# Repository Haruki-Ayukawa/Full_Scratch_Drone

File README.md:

# Full_Scratch_Drone
## 概要
キットを購入するのではなく<br>
- KiCADで設計し表面実装したESP32搭載制御基板
- 3DCADで設計し3Dプリンタで造形したフレーム
- AmazonやRCヘリドローン専門ショップで購入したモータ・プロペラ・LiPoバッテリ

を用いてフルスクラッチのドローンを製作しました。

## 制御基板
- 構成 → MCU(マイコン)＋IMU(9軸慣性センサ)＋ESC(MOSFET×4個)＋コネクタなどを1枚の基板に搭載しました。
- 部品 → ESP32-MINI-1-N4(MCU)、ICM-20948(IMU)、AO3400A(Nch MOSFET)などなど。
- 購入 → 秋月電子通商　様やcorestaff　様で購入しました。一部のパーツはAmazonで購入しました。
- 基板 → SnapMagicなどでパーツのデータを収集し、KiCADで回路図及びPCB基板を設計後、JLCPCBに発注しました。
- 実装 → ホットプレートやペーストはんだを用いて表面実装しました。

詳細は[control-boardフォルダ](control-board)をご覧ください。

## フレーム
- 設計 → Fusionで設計しました。
- 製造 → 3Dプリンタ(RAISE3D E2　ノズル径0.4mm　フィラメントPLA黒色)で造形しました。

詳細は[frameフォルダ](frame)をご覧ください。

## モータ
- 部品 → [直径8.5mm　長さ20mm　3~5V](https://amzn.asia/d/07lUeh3T)
- 購入 → Amazonで購入しました。

## プロペラ
- 部品 → [マイクロクワッド用55mm Blade Propeller Prop 4pcs](https://wda-jp.com/shop/products/detail/863)
- 購入 → 若狭小浜ドローン協会(WDA) 様の公式オンラインショップで購入しました。

## LiPoバッテリ
- 部品 → [GNB POWER LIPO 550mAh 1s 3.8V 100C コネクタ種：A30](https://helimonster.jp/?pid=176671622)
- 購入 → ヘリモンスター　様で購入しました。

## 制御コード(フライトコントローラ：ドローン側)
- VSCodeでコーディングし、VSCodeの拡張機能であるPlatformIOでコンパイルとビルドを行いました。

詳細は[firmwareフォルダ]()をご覧ください。

## 制御コード(プロポーショナルコントロール送信機：スマホアプリ側)
- MIT App Inventorというブラウザタイプのアプリ開発ツールを用いてスマホをドローンのプロポにしました。

詳細は別のリポジトリ[Example_MITAppInventor_for_DroneController](https://github.com/Haruki-Ayukawa/Example_MITAppInventor_for_DroneController/tree/main)をご覧ください。

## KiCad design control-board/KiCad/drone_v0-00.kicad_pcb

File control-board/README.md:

# control-boardフォルダの中身について
## KiCadフォルダ

## manufacturingフォルダ

## docsフォルダ

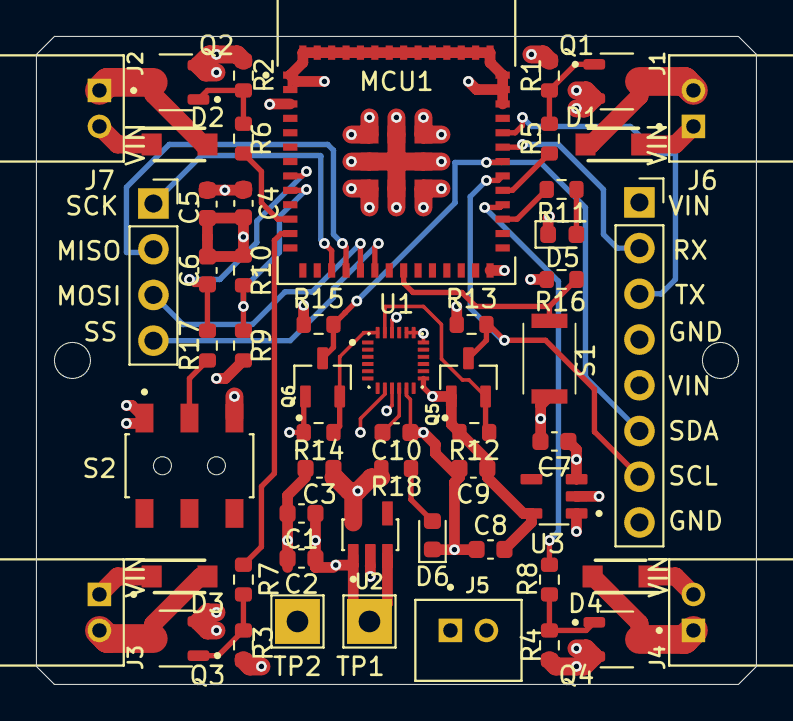
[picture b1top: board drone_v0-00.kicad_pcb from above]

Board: 4 copper layers, 40.0 x 36.0 mm, 55 parts (0 on the bottom side), 34 nets.

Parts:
C1, C3, C4: 10µ; C_0603_1608Metric
C2, C5, C9, C10: 0.1µ; C_0603_1608Metric
C6, C7, C8: 1µ; C_0603_1608Metric
D1, D2, D3, D4: SS34FA; SODFL3618X143N
D5, D6: LED; LED_0603_1608Metric
J1, J2, J3, J4: S2B-PH-K-S_LF__SN_; JST_S2B-PH-K-S_LF__SN_
J5: B2B-PH-K-S_LF__SN_; JST_B2B-PH-K-S_LF__SN_
J6: Conn_01x08_Pin; PinSocket_1x08_P2.54mm_Vertical
J7: Conn_01x04_Pin; PinSocket_1x04_P2.54mm_Vertical
MCU1: ESP32-MINI-1-N4; XCVR_ESP32-MINI-1-N4
Q1, Q2, Q3, Q4: AO3400A; SOT95P280X125-3N
Q5, Q6: BSS138; SOT95P240X111-3N
R1, R2, R3, R4, R9, R10, R16, R17: 10k; R_0603_1608Metric
R5, R6, R7, R8: 22; R_0603_1608Metric
R11: 470; R_0603_1608Metric
R12, R13, R14, R15, R18: 2.2k; R_0603_1608Metric
S1: SKRKAEE020
S2: SLW-713515-2A-SMT-TR; SW_SLW-713515-2A-SMT-TR
TP1, TP2: TestPoint; TestPoint_THTPad_2.5x2.5mm_Drill1.2mm
U1: ICM-20948; QFN40P300X300X105-24N
U2: AP2112K-3.3TRG1; SOT95P285X140-5N
U3: LP5907MFX-1.8_NOPB; SOT95P280X145-5N

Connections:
+1V8: C8.1, C9.1, Q5.1, Q6.1, R12.1, R14.1, U1.8 (VDDIO), U1.13 (VDD), U1.22 (~CS), U3.5 (OUT)
+3V3: C3.1, C4.1, C5.1, MCU1.3 (3V3), R13.1, R15.1, R16.1, R18.1, S2.3, U2.5 (VOUT)
+BATT: C1.1, C2.1, C7.1, D1.1 (K), D2.1 (K), D3.1 (K), D4.1 (K), J1.1, J2.2, J3.1, J4.2, J5.2, J6.1, J6.5, R9.1, TP1.1, U2.1 (VIN), U2.3 (EN), U3.1 (IN), U3.3 (EN)
/ADC: MCU1.9 (I34), R9.2, R10.1
/MISO: J7.2, MCU1.17 (IO12)
/MOSI: J7.3, MCU1.18 (IO13)
/MOTOR_1: MCU1.32 (IO19), R5.1
/MOTOR_2: MCU1.11 (IO32), R6.1
/MOTOR_3: MCU1.12 (IO33), R7.1
/MOTOR_4: MCU1.31 (IO23), R8.1
/RX: J6.2, MCU1.35 (RXD0)
/SCK: J7.1, MCU1.16 (IO14)
/SCL: Q5.2, R12.2, U1.23 (SCL/SCLK)
/SCL_MCU: J6.7, MCU1.33 (IO22), Q5.3, R13.2
/SDA: Q6.2, R14.2, U1.24 (SDA/SDI)
/SDA_MCU: J6.6, MCU1.34 (IO21), Q6.3, R15.2
/SS: J7.4, MCU1.19 (IO15)
/TX: J6.3, MCU1.36 (TXD0)
GND: C1.2, C2.2, C3.2, C4.2, C5.2, C6.2, C7.2, C8.2, C9.2, C10.2, D5.1 (K), D6.1 (K), J5.1, J6.4, J6.8, MCU1.1 (GND_1), MCU1.2 (GND_1), MCU1.27 (GND_1), MCU1.38 (GND_1), MCU1.39 (GND_1), MCU1.40 (GND_1), MCU1.41 (GND_1), MCU1.42 (GND_1), MCU1.43 (GND_1), MCU1.44 (GND_1), MCU1.45 (GND_1), MCU1.46 (GND_1), MCU1.47 (GND_1), MCU1.48 (GND_1), MCU1.49 (GND_1), MCU1.50 (GND_2), MCU1.51 (GND_2), MCU1.52 (GND_2), MCU1.53 (GND_2), MCU1.54 (GND_2), MCU1.55_1 (GND_2), MCU1.55_2 (GND_2), MCU1.55_3 (GND_2), MCU1.55_4 (GND_2), MCU1.55_5 (GND_2), MCU1.55_6 (GND_2), MCU1.55_7 (GND_2), MCU1.55_8 (GND_2), MCU1.55_9 (GND_2), Q1.2, Q2.2, Q3.2, Q4.2, R1.2, R2.2, R3.2, R4.2, R10.2, S1.2, S2.1, TP2.1, U1.9 (AD0/SDO), U1.11 (FSYNC), U1.18 (GND), U1.19 (RESV_19), U1.20 (RESV_20), U2.2 (GND), U3.2 (GND)
unnamed: D1.2 (A), J1.2, Q1.3
unnamed: D2.2 (A), J2.1, Q2.3
unnamed: D3.2 (A), J3.2, Q3.3
unnamed: D4.2 (A), J4.1, Q4.3
unnamed: D5.2 (A), R11.2
unnamed: D6.2 (A), R18.2
unnamed: C6.1, MCU1.8 (EN), R17.2
unnamed: MCU1.21 (IO0), R16.2, S1.1
unnamed: MCU1.30 (IO18), R11.1
unnamed: Q1.1, R1.1, R5.2
unnamed: Q2.1, R2.1, R6.2
unnamed: Q3.1, R3.1, R7.2
unnamed: Q4.1, R4.1, R8.2
unnamed: R17.1, S2.2
unnamed: C10.1, U1.10 (REGOUT)

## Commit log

2026-04-09 Rename control-board/drone_v0-00.kicad_pro to control-board/KiCad/drone_v0-00.kicad_pro
2026-04-09 Rename control-board/drone_v0-00_GBR.zip to control-board/manufacturing/drone_v0-00_GBR.zip
2026-04-09 Rename frame/v0-00_上から.JPG to frame/docs/v0-00_上から.JPG
